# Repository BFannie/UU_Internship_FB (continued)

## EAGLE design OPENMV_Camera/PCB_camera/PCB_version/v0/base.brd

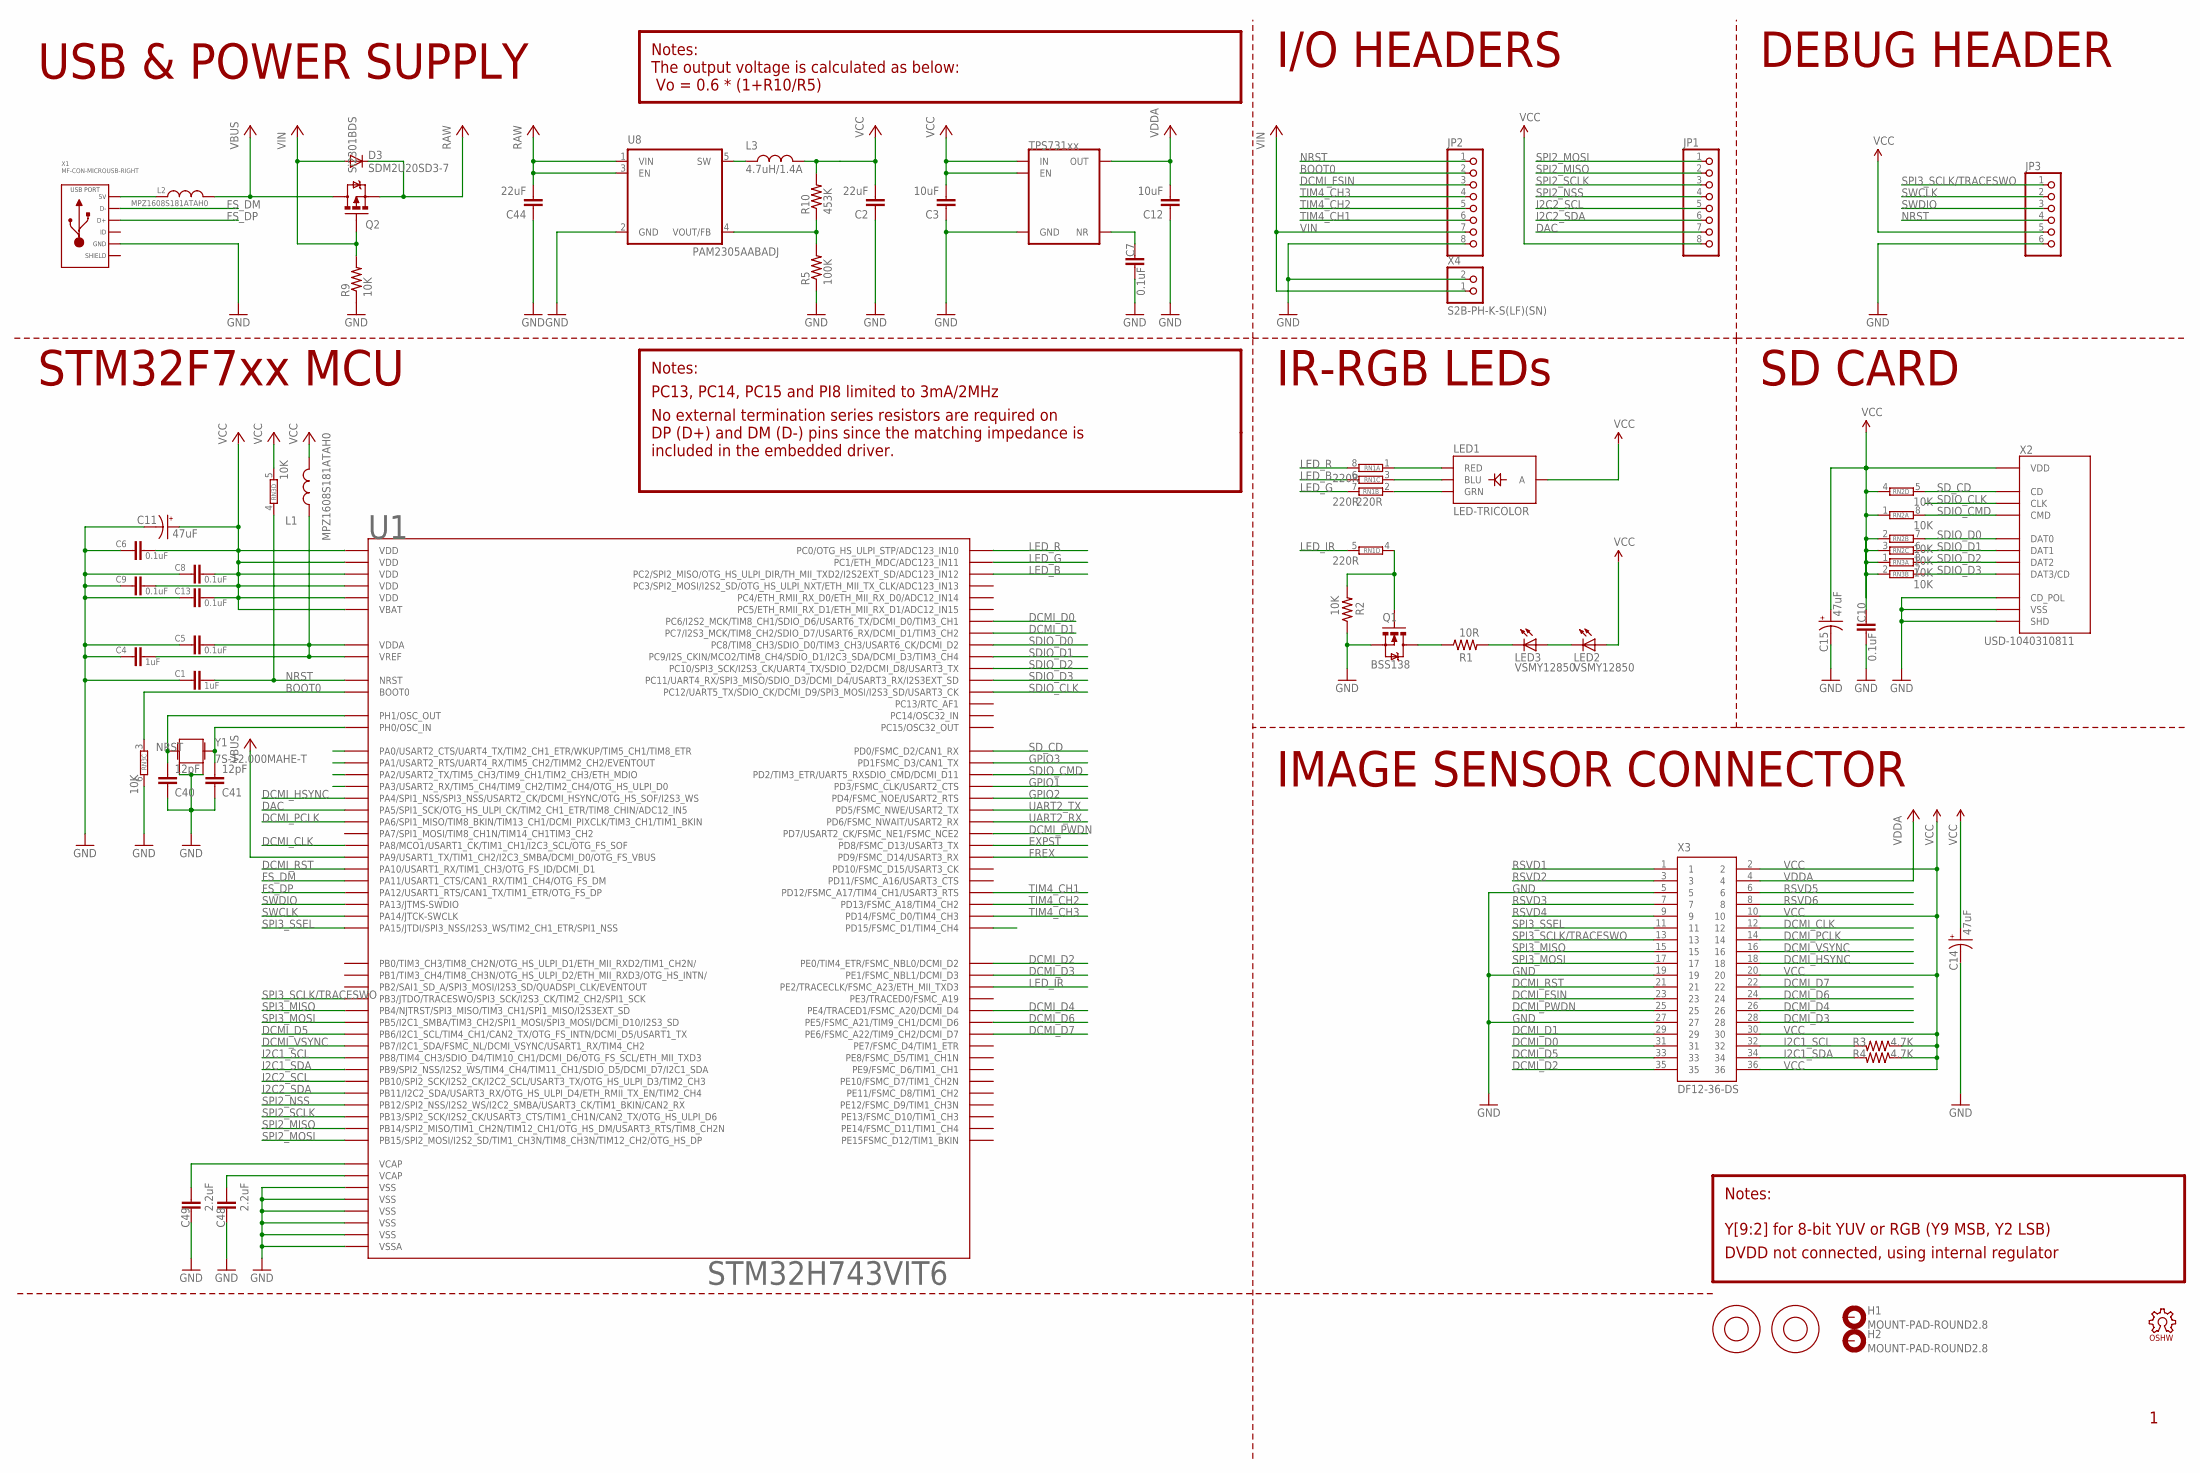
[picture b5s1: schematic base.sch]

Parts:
C1, C4: 1uF; 0603-CAP
C2, C44: 22uF; 0805
C3, C12: 10uF; 0805
C5, C6, C7, C8, C9, C10, C13: 0.1uF; 0603-CAP
C11, C14, C15: 47uF; EIA3216
C40, C41: 12pF; 0603-CAP
C48, C49: 2.2uF; 0603-CAP
D3: SDM2U20SD3-7; SOD-323
H1, H2: MOUNT-PAD-ROUND2.8; 2,8-PAD
JP1, JP2: PINHD-1X8; 1X08
JP3: PINHD-1X6; 1X06
L1, L2: MPZ1608S181ATAH0; 0603
L3: 4.7uH/1.4A; 1007
LED1: LED-TRICOLOR; LED-TRICOLOR-SMD-MF
LED2, LED3: VSMY12850; LED-1206
LOGO1: OSHW_LOGO_FILLX0100-NT; OSHW_FILLX100_NOTEXT
M1, M2: 9774030243R; 9774030151R
Q1: BSS138; SOT23-3
Q2: Si2301BDS; SOT23-3
R1: 10R; 0603-RES
R2, R9: 10K; 0603-RES
R3, R4: 4.7K; 0603-RES
R5: 100K; 0603-RES
R10: 453K; 0603-RES
RN1: 220R; EXBV8V
RN2, RN3: 10K; EXBV8V
U1: STM32H743VIT6; LQFP100
U5: TPS731XX; SOT23-5
U8: PAM2305AABADJ; TSOT25
X1: MF-CON-MICROUSB-RIGHT; MICROUSB-RIGHT
X2: USD-1040310811; 1040310811
X3: DF12-36-DS
X4: S2B-PH-K-S(LF)(SN); JST-PH-2-THM-RA
Y1: 7S-12.000MAHE-T; CRYSTAL-2.5X2.0

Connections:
BOOT0: JP2.2, RN3.3 (1), U1.94 (BOOT0)
DAC: JP1.7, U1.29 (PA5/SPI1_SCK/OTG_HS_ULPI_CK/TIM2_CH1_ET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)
DCMI_CLK: U1.67 (PA8/MCO1/USART1_CK/TIM1_CH1/I2C3_SCL/OT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), X3.12
DCMI_D0: U1.63 (PC6/I2S2_MCK/TIM8_CH1/SDIO_D6/USART6_TX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), X3.31
DCMI_D1: U1.64 (PC7/I2S3_MCK/TIM8_CH2/SDIO_D7/USART6_RX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), X3.29
DCMI_D2: U1.97 (PE0/TIM4_ETR/FSMC_NBL0/DCMI_D2), X3.35
DCMI_D3: U1.98 (PE1/FSMC_NBL1/DCMI_D3), X3.28
DCMI_D4: U1.3 (PE4/TRACED1/FSMC_A20/DCMI_D4), X3.26
DCMI_D5: U1.92 (PB6/I2C1_SCL/TIM4_CH1/CAN2_TX/OTG_FS_IN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), X3.33
DCMI_D6: U1.4 (PE5/FSMC_A21/TIM9_CH1/DCMI_D6), X3.24
DCMI_D7: U1.5 (PE6/FSMC_A22/TIM9_CH2/DCMI_D7), X3.22
DCMI_FSIN: JP2.3, X3.23
DCMI_HSYNC: U1.28 (PA4/SPI1_NSS/SPI3_NSS/USART2_CK/DCMI_HS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), X3.18
DCMI_PCLK: U1.30 (PA6/SPI1_MISO/TIM8_BKIN/TIM13_CH1/DCMI_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), X3.14
DCMI_PWDN: U1.88 (PD7/USART2_CK/FSMC_NE1/FSMC_NCE2), X3.25
DCMI_RST: U1.69 (PA10/USART1_RX/TIM1_CH3/OTG_FS_ID/DCMI_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), X3.21
DCMI_VSYNC: U1.93 (PB7/I2C1_SDA/FSMC_NL/DCMI_VSYNC/USART1_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), X3.16
EXPST: U1.55 (PD8/FSMC_D13/USART3_TX)
FREX: U1.56 (PD9/FSMC_D14/USART3_RX)
FS_DM: U1.70 (PA11/USART1_CTS/CAN1_RX/TIM1_CH4/OTG_FS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), X1.2 (D-)
FS_DP: U1.71 (PA12/USART1_RTS/CAN1_TX/TIM1_ETR/OTG_FS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), X1.3 (D+)
GND: C1.2, C2.1, C3.1, C4.2, C5.2, C6.2, C7.2, C8.2, C9.2, C10.2, C11.C (-), C12.1, C13.2, C14.C (-), C15.C (-), C40.1, C41.1, C44.1, C48.2, C49.2, JP2.8, JP3.6, Q1.2 (S), R2.1, R5.1, R9.1, RN3.6 (2), U1.10 (VSS), U1.19 (VSSA), U1.26 (VSS), U1.49 (VSS), U1.74 (VSS), U1.99 (VSS), U5.2 (GND), U8.2 (GND), X1.5 (GND), X2.CD$2 (CD_POL), X2.G$1 (SHD), X2.G$2 (SHD), X2.G$3 (SHD), X2.G$4 (SHD), X2.P$6 (VSS), X3.5, X3.19, X3.27, X4.2 (1), Y1.2, Y1.4
GPIO1: U1.84 (PD3/FSMC_CLK/USART2_CTS)
GPIO2: U1.85 (PD4/FSMC_NOE/USART2_RTS)
GPIO3: U1.82 (PD1FSMC_D3/CAN1_TX)
I2C1_SCL: R3.2, U1.95 (PB8/TIM4_CH3/SDIO_D4/TIM10_CH1/DCMI_D6/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), X3.32
I2C1_SDA: R4.2, U1.96 (PB9/SPI2_NSS/I2S2_WS/TIM4_CH4/TIM11_CH1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), X3.34
I2C2_SCL: JP1.5, U1.46 (PB10/SPI2_SCK/I2S2_CK/I2C2_SCL/USART3_T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)
I2C2_SDA: JP1.6, U1.47 (PB11/I2C2_SDA/USART3_RX/OTG_HS_ULPI_D4/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)
LED_B: RN1.6 (2), U1.17 (PC2/SPI2_MISO/OTG_HS_ULPI_DIR/TH_MII_TX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)
LED_G: RN1.7 (2), U1.16 (PC1/ETH_MDC/ADC123_IN11)
LED_IR: RN1.5 (2), U1.1 (PE2/TRACECLK/FSMC_A23/ETH_MII_TXD3)
LED_R: RN1.8 (2), U1.15 (PC0/OTG_HS_ULPI_STP/ADC123_IN10)
unnamed: C40.2, U1.13 (PH1/OSC_OUT), Y1.3 (2)
unnamed: C41.2, U1.12 (PH0/OSC_IN), Y1.1
unnamed: Q1.1 (G), R2.2, RN1.4 (1)
unnamed: LED1.B (BLU), RN1.3 (1)
unnamed: L2.1, X1.1 (5V)
unnamed: LED1.R (RED), RN1.1
unnamed: LED1.G (GRN), RN1.2 (1)
unnamed: LED3.C, R1.2
unnamed: C7.1, U5.4 (NR)
unnamed: C4.1, C5.1, L1.1, U1.20 (VREF), U1.21 (VDDA)
unnamed: R5.2, R10.1, U8.4 (VOUT/FB)
unnamed: Q1.3 (D), R1.1
unnamed: LED2.C, LED3.A
NRST: C1.1, JP2.1, JP3.4, RN3.4 (1), U1.14 (NRST)
RAW: C44.2, D3.1 (C), Q2.2 (S), U8.1 (VIN), U8.3 (EN)
RSVD1: X3.1
RSVD2: X3.3
RSVD3: X3.7
RSVD4: X3.9
RSVD5: X3.6
RSVD6: X3.8
SDIO_CLK: U1.80 (PC12/UART5_TX/SDIO_CK/DCMI_D9/SPI3_MOSI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), X2.P$5 (CLK)
SDIO_CMD: RN2.8 (2), U1.83 (PD2/TIM3_ETR/UART5_RXSDIO_CMD/DCMI_D11), X2.P$3 (CMD)
SDIO_D0: RN2.7 (2), U1.65 (PC8/TIM8_CH3/SDIO_D0/TIM3_CH3/USART6_CK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), X2.P$7 (DAT0)
SDIO_D1: RN2.6 (2), U1.66 (PC9/I2S_CKIN/MCO2/TIM8_CH4/SDIO_D1/I2C3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), X2.P$8 (DAT1)
SDIO_D2: RN3.8 (2), U1.78 (PC10/SPI3_SCK/I2S3_CK/UART4_TX/SDIO_D2/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), X2.P$1 (DAT2)
SDIO_D3: RN3.7 (2), U1.79 (PC11/UART4_RX/SPI3_MISO/SDIO_D3/DCMI_D4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), X2.P$2 (DAT3/CD)
SD_CD: RN2.5 (2), U1.81 (PD0/FSMC_D2/CAN1_RX), X2.CD$1 (CD)
SPI2_MISO: JP1.2, U1.53 (PB14/SPI2_MISO/TIM1_CH2N/TIM12_CH1/OTG_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)
SPI2_MOSI: JP1.1, U1.54 (PB15/SPI2_MOSI/I2S2_SD/TIM1_CH3N/TIM8_C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)
SPI2_NSS: JP1.4, U1.51 (PB12/SPI2_NSS/I2S2_WS/I2C2_SMBA/USART3_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)
SPI2_SCLK: JP1.3, U1.52 (PB13/SPI2_SCK/I2S2_CK/USART3_CTS/TIM1_C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)
SPI3_MISO: U1.90 (PB4/NJTRST/SPI3_MISO/TIM3_CH1/SPI1_MISO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), X3.15
SPI3_MOSI: U1.91 (PB5/I2C1_SMBA/TIM3_CH2/SPI1_MOSI/SPI3_M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), X3.17
SPI3_SCLK/TRACESWO: JP3.1, U1.89 (PB3/JTDO/TRACESWO/SPI3_SCK/I2S3_CK/TIM2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), X3.13
SPI3_SSEL: U1.77 (PA15/JTDI/SPI3_NSS/I2S3_WS/TIM2_CH1_ETR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), X3.11
SW: L3.1, U8.5 (SW)
SWCLK: JP3.2, U1.76 (PA14/JTCK-SWCLK)
SWDIO: JP3.3, U1.72 (PA13/JTMS-SWDIO)
TIM4_CH1: JP2.6, U1.59 (PD12/FSMC_A17/TIM4_CH1/USART3_RTS)
TIM4_CH2: JP2.5, U1.60 (PD13/FSMC_A18/TIM4_CH2)
TIM4_CH3: JP2.4, U1.61 (PD14/FSMC_D0/TIM4_CH3)
UART2_RX: U1.87 (PD6/FSMC_NWAIT/USART2_RX)
UART2_TX: U1.86 (PD5/FSMC_NWE/USART2_TX)
VBUS: L2.2, Q2.3 (D), U1.68 (PA9/USART1_TX/TIM1_CH2/I2C3_SMBA/DCMI_D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)
VCAP1: C49.1, U1.48 (VCAP)
VCAP2: C48.1, U1.73 (VCAP)
VCC: C2.2, C3.2, C6.1, C8.1, C9.1, C10.1, C11.A (+), C13.1, C14.A (+), C15.A (+), JP1.8, JP3.5, L1.2, L3.2, LED1.A, LED2.A, R3.1, R4.1, R10.2, RN2.1, RN2.2 (1), RN2.3 (1), RN2.4 (1), RN3.1, RN3.2 (1), RN3.5 (2), U1.6 (VBAT), U1.11 (VDD), U1.27 (VDD), U1.50 (VDD), U1.75 (VDD), U1.100 (VDD), U5.1 (IN), U5.3 (EN), X2.P$4 (VDD), X3.2, X3.10, X3.20, X3.30, X3.36
VDDA: C12.2, U5.5 (OUT), X3.4
VIN: D3.2 (A), JP2.7, Q2.1 (G), R9.2, X4.1 (2)

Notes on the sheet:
PC13, PC14, PC15 and PI8 limited to 3mA/2MHz
SD CARD
Y[9:2] for 8-bit YUV or RGB (Y9 MSB, Y2 LSB)
DVDD not connected, using internal regulator
Notes:
IMAGE SENSOR CONNECTOR
STM32F7xx MCU
IR-RGB LEDs
USB & POWER SUPPLY
DEBUG HEADER
I/O HEADERS
No external termination series resistors are required on DP (D+) and DM (D-) pins since the matching impedance is included in the embedded driver.
The output voltage is calculated as below: Vo = 0.6 * (1+R10/R5)

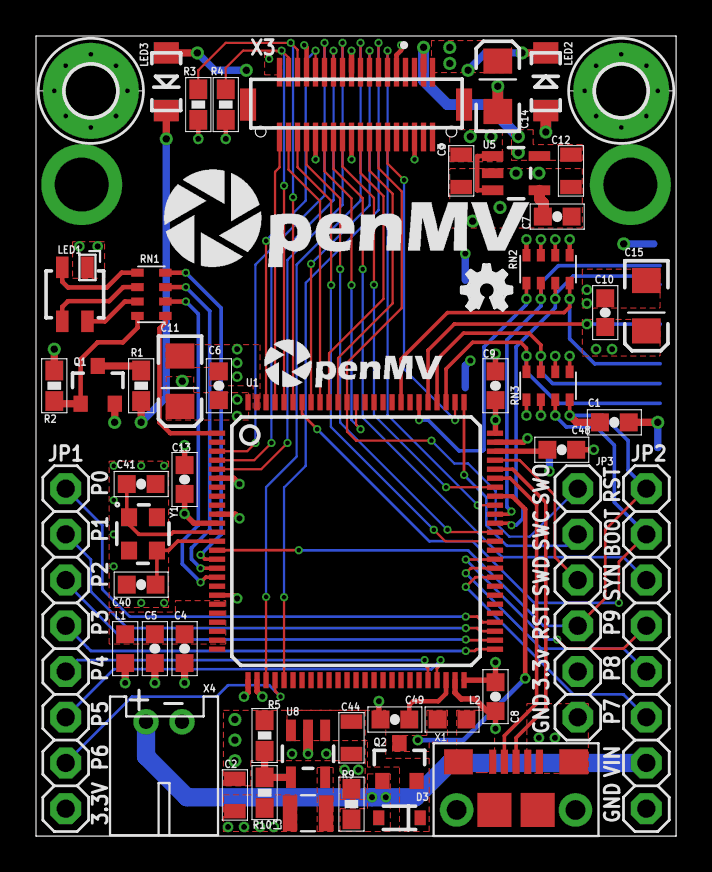
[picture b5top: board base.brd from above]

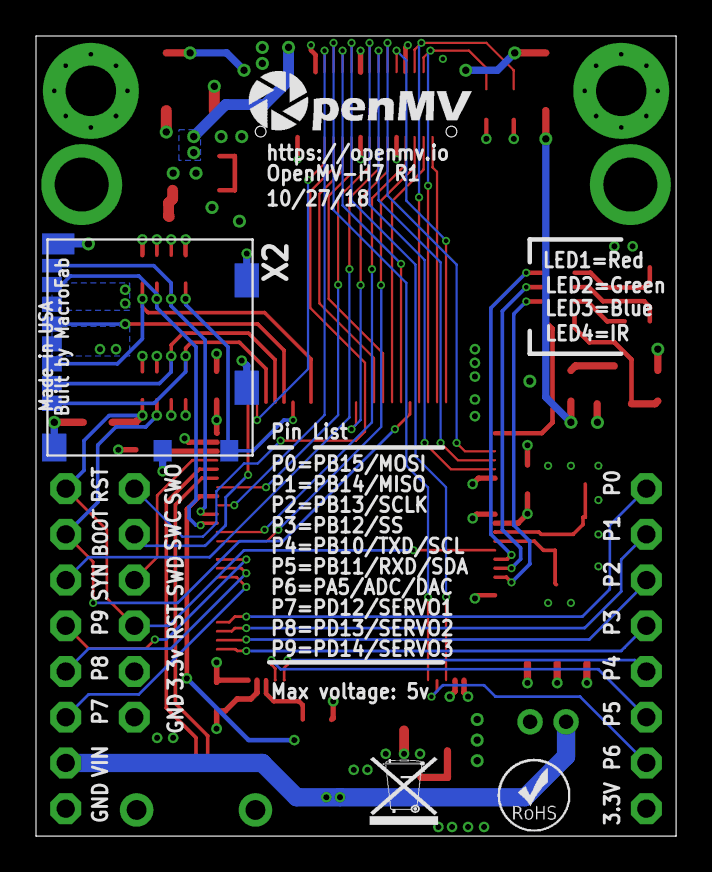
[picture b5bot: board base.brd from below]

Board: 4 copper layers, 35.6 x 44.5 mm, 60 parts (4 on the bottom side), 70 nets.

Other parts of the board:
U$1: WEEE
U$2: ROHS
U$3: OMV-LOGO
U$4: OMV-LOGO-SMALL
U$6: OMV-LOGO-BIG

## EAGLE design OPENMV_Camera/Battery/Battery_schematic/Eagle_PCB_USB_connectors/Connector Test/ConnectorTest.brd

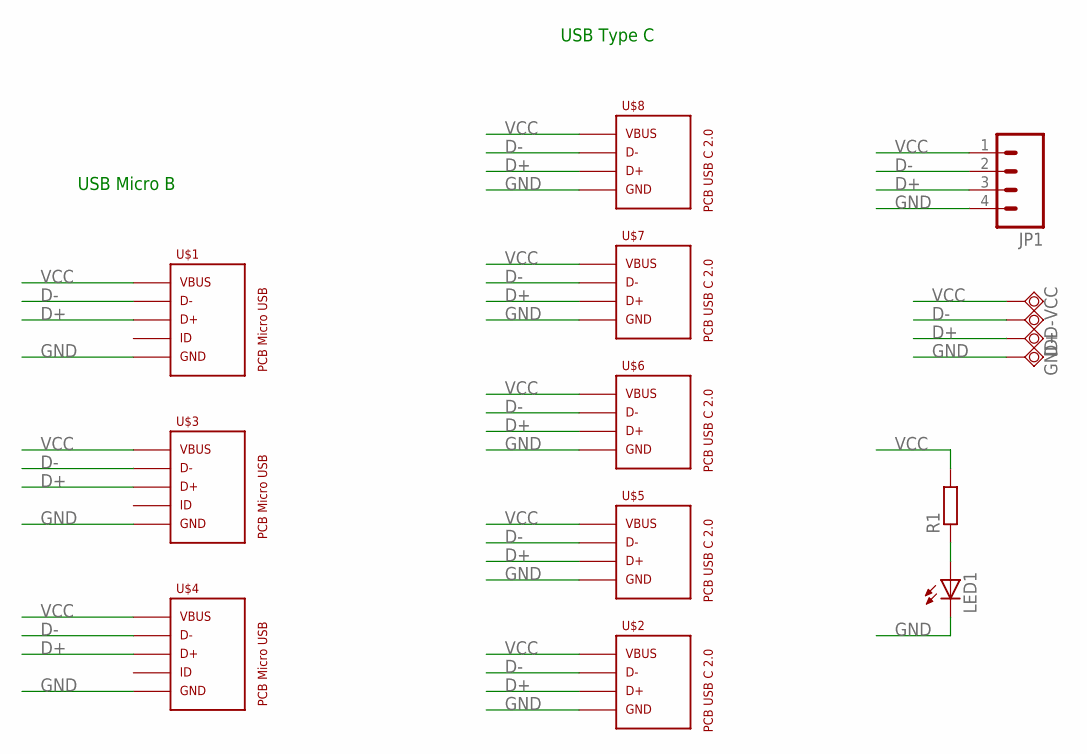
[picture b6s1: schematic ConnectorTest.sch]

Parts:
D+: TPSQTP20SQ; TP20SQ
D-: TPSQTP20SQ; TP20SQ
GND: TPSQTP20SQ; TP20SQ
JP1: M04LONGPADS; 1X04_LONGPADS
LED1: LEDSMT1206; 1206
R1: R-EU_R1206; R1206
U$1: PCB_MICRO_USB_BDSW_2; USB_TYPE_B_DSW_2
U$2: PCB_USB_C_2.0W_1; USB_TYPE_C_W_2.0_1
U$3: PCB_MICRO_USB_BDSW_3; USB_TYPE_B_DSW_3
U$4: PCB_MICRO_USB_BDSW_1; USB_TYPE_B_DSW_1
U$5: PCB_USB_C_2.0W_2; USB_TYPE_C_W_2.0_2
U$6: PCB_USB_C_2.0W_3; USB_TYPE_C_W_2.0_3
U$7: PCB_USB_C_2.0W_4; USB_TYPE_C_W_2.0_4
U$8: PCB_USB_C_2.0W_5; USB_TYPE_C_W_2.0_5
VCC: TPSQTP20SQ; TP20SQ

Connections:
D+: D+.TP, JP1.3, U$1.3D (3), U$2.D+, U$3.3D (3), U$4.3D (3), U$5.D+, U$6.D+, U$7.D+, U$8.D+
D-: D-.TP, JP1.2, U$1.2D (2), U$2.D-, U$3.2D (2), U$4.2D (2), U$5.D-, U$6.D-, U$7.D-, U$8.D-
GND: GND.TP, JP1.4, LED1.C, U$1.5D (5), U$2.GND, U$3.5D (5), U$4.5D (5), U$5.GND, U$6.GND, U$7.GND, U$8.GND
unnamed: LED1.A, R1.1
VCC: JP1.1, R1.2, U$1.1D (1), U$2.VBUS, U$3.1D (1), U$4.1D (1), U$5.VBUS, U$6.VBUS, U$7.VBUS, U$8.VBUS, VCC.TP

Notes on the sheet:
USB Micro B
USB Type C

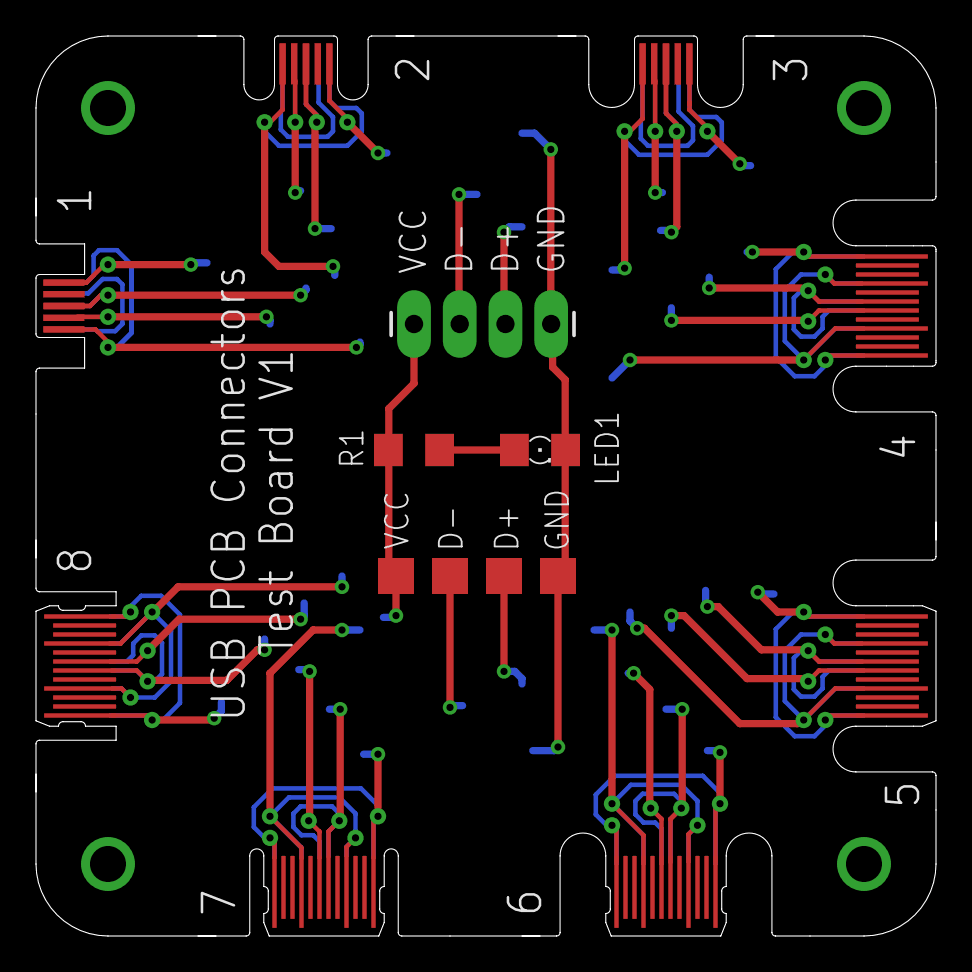
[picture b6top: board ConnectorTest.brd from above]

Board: 2 copper layers, 50.0 x 50.0 mm, 15 parts (0 on the bottom side), 5 nets.
